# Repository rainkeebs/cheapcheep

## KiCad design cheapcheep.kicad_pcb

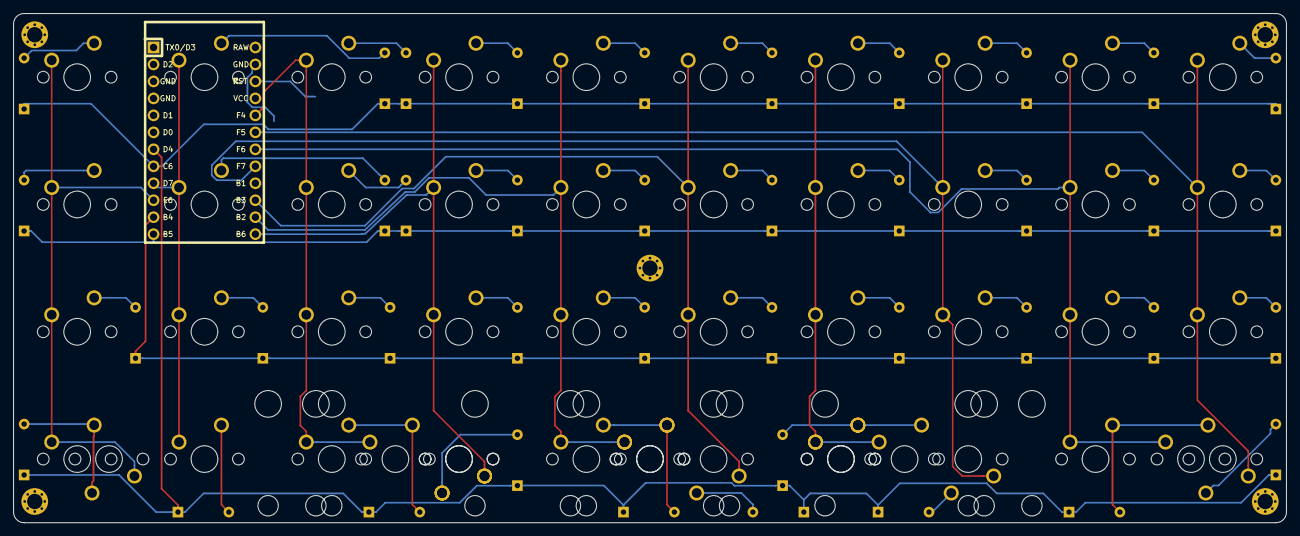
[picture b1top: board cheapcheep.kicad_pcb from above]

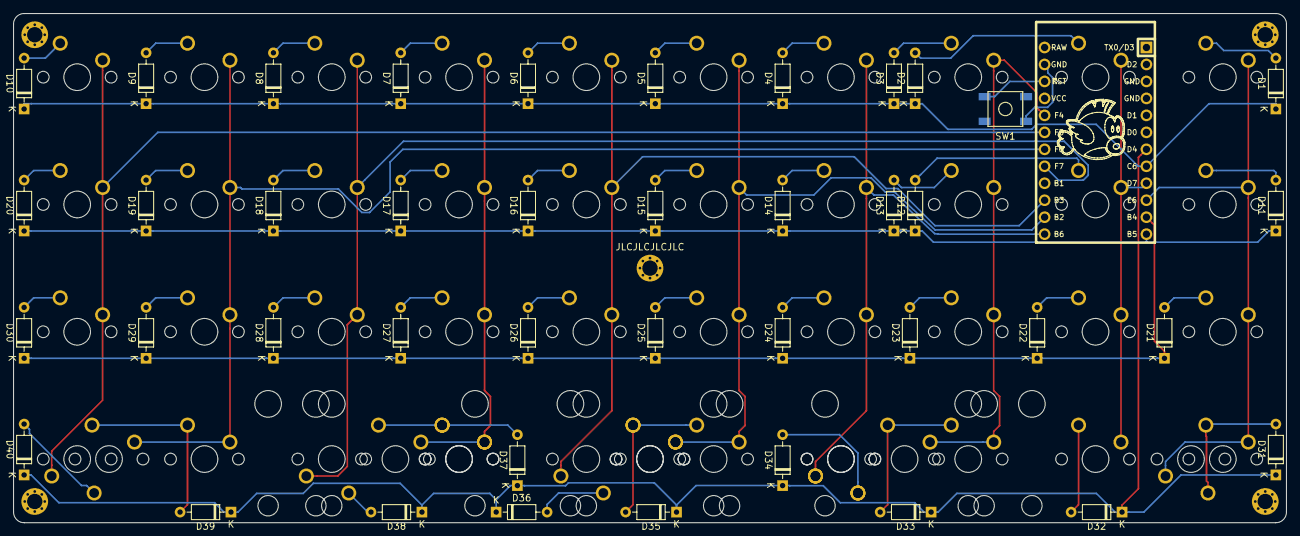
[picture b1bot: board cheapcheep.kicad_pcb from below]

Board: 2 copper layers, 190.5 x 76.2 mm, 95 parts (41 on the bottom side), 56 nets.

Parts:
D1, D2, D3, D4, D5, D6, D7, D8, D9, D10, D11, D12, D13, D14, D15, D16, D17, D18, D19, D20, D21, D22, D23, D24, D25, D26, D27, D28, D29, D30, D31, D32, D33, D34, D35, D36, D37, D38, D39, D40: D_Small; D_DO-35_SOD27_P7.62mm_Horizontal
MX1, MX2, MX3, MX4, MX5, MX6, MX7, MX8, MX9, MX10, MX11, MX12, MX13, MX14, MX15, MX16, MX17, MX18, MX19, MX20, MX21, MX22, MX23, MX24, MX25, MX26, MX27, MX28, MX29, MX30, MX32, MX33, MX34, MX35, MX36, MX37, MX38, MX39, MX40, MX41: MX-NoLED; MXOnly-1U-NoLED
MX31: MX-NoLED; MXOnly-7U-ReversedStabilizers-NoLED
MX42, MX47: MX-NoLED; MXOnly-1.5U-NoLED
MX43, MX45, MX46: MX-NoLED; MXOnly-2U-ReversedStabilizers-NoLED
MX44: MX-NoLED; MXOnly-3U-NoLED
MX48: MX-NoLED; MXOnly-3U-ReversedStabilizers-NoLED
Ref**: Val**; M2_HOLE_v3
Ref**#2, Ref**#3, Ref**#4, Ref**#5: Val**; M2_HOLE_v3
SW1: SW_Push; SKQG-1155865
U1: ProMicro; ArduinoProMicro

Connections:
COL0: MX1.1, MX11.1, MX21.1, MX32.1, MX42.1, U1.10
COL1: MX2.1, MX12.1, MX22.1, MX33.1, U1.9
COL2: MX3.1, MX13.1, MX23.1, MX34.1, MX43.1, U1.20
COL3: MX4.1, MX14.1, MX24.1, MX35.1, MX44.1, U1.13
COL4: MX5.1, MX15.1, MX25.1, MX31.1, MX36.1, MX45.1, U1.14
COL5: MX6.1, MX16.1, MX26.1, MX37.1, U1.15
COL6: MX7.1, MX17.1, MX27.1, MX38.1, MX46.1, MX48.1, U1.16
COL7: MX8.1, MX18.1, MX28.1, MX39.1, U1.17
COL8: MX9.1, MX19.1, MX29.1, MX40.1, MX47.1, U1.18
COL9: MX10.1, MX20.1, MX30.1, MX41.1, U1.19
unnamed: D1.2, MX1.2
unnamed: D2.2, MX2.2
unnamed: D3.2, MX3.2
unnamed: D4.2, MX4.2
unnamed: D5.2, MX5.2
unnamed: D6.2, MX6.2
unnamed: D7.2, MX7.2
unnamed: D8.2, MX8.2
unnamed: D9.2, MX9.2
unnamed: D10.2, MX10.2
unnamed: D11.2, MX11.2
unnamed: D12.2, MX12.2
unnamed: D13.2, MX13.2
unnamed: D14.2, MX14.2
unnamed: D15.2, MX15.2
unnamed: D16.2, MX16.2
unnamed: D17.2, MX17.2
unnamed: D18.2, MX18.2
unnamed: D19.2, MX19.2
unnamed: D20.2, MX20.2
unnamed: D21.2, MX21.2
unnamed: D22.2, MX22.2
unnamed: D23.2, MX23.2
unnamed: D24.2, MX24.2
unnamed: D25.2, MX25.2
unnamed: D26.2, MX26.2
unnamed: D27.2, MX27.2
unnamed: D28.2, MX28.2
unnamed: D29.2, MX29.2
unnamed: D30.2, MX30.2
unnamed: D31.2, MX32.2, MX42.2
unnamed: D32.2, MX33.2
unnamed: D33.2, MX34.2, MX43.2
unnamed: D34.2, MX35.2, MX44.2
unnamed: D35.2, MX31.2, MX36.2, MX45.2
unnamed: D36.2, MX37.2
unnamed: D37.2, MX38.2, MX46.2, MX48.2
unnamed: D38.2, MX39.2
unnamed: D39.2, MX40.2, MX47.2
unnamed: D40.2, MX41.2
unnamed: SW1.1, U1.23
unnamed: SW1.2, U1.22
ROW0: D1.1, D2.1, D3.1, D4.1, D5.1, D6.1, D7.1, D8.1, D9.1, D10.1, U1.8
ROW1: D11.1, D12.1, D13.1, D14.1, D15.1, D16.1, D17.1, D18.1, D19.1, D20.1, U1.12
ROW2: D21.1, D22.1, D23.1, D24.1, D25.1, D26.1, D27.1, D28.1, D29.1, D30.1, U1.11
ROW3: D31.1, D32.1, D33.1, D34.1, D35.1, D36.1, D37.1, D38.1, D39.1, D40.1, U1.7

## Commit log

2020-10-26 initial
2020-10-26 done
2020-10-26 gerbies added
2020-10-26 gerbs updated and stuff
